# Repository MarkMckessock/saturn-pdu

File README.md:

# saturn-pdu

**A 1U rack PDU delivering six independently switched and metered 19V outputs,
for a six-node Minisforum MS-01 Kubernetes cluster.**

> **Status: draft specification. Nothing here has been built or bench-verified.**
> Every figure is analytical. Do not fabricate from this repository yet.

Derived from [Shrike-Lab/HomeLab-PDU-V1](https://github.com/Shrike-Lab/HomeLab-PDU-V1).
Licensed **CERN-OHL-S v2** (strongly reciprocal) -- see [`LICENSE`](LICENSE) and
[`NOTICE`](NOTICE).

---

## The problem

Six MS-01 nodes, six 180W bricks, six mains outlets, twelve cables, and no way
to see what any node draws or to power-cycle a wedged one without walking to the
rack.

## What this is

One 1U box: a single mains inlet, six 19V outputs, each switchable over the
network and each reporting volts, amps and watts.

```
IEC inlet ──► RSP-1000-48 ──► 48V bus ─┬──► [2ch board A] ──► ports 1,2
                  ▲                     ├──► [2ch board B] ──► ports 3,4
           remote ON/OFF                └──► [2ch board C] ──► ports 5,6
           (front button)                          │
                                          [control board]
                                          ESP32-S3 + wired Ethernet
                                          6x INA226 telemetry
                                          Prometheus /metrics
```

Each channel is an LM5116 synchronous buck, 48V down to 19V at 7A, with its own
fuse, its own current limit, and its own overvoltage crowbar that works **with
the microcontroller unpowered**.

## Three design rules that explain most of the decisions

1. **Outputs fail ON.** Channels are held on by resistors. The MCU can only turn
   one *off*, by actively pulling a pin down. An MCU that is crashed,
   unprogrammed, unpowered or physically removed leaves every node running.
   No firmware path may ever de-energise an output autonomously.
2. **Protection does not depend on software.** A shorted high-side transistor
   puts 48V on a 19V input and destroys a node. Disabling its controller
   achieves nothing when the transistor is a short, so each output carries an
   SCR crowbar with its own reference, powered from its own output.
3. **The display cannot break anything.** It is a separate device on a UART
   link, not the controller. Unplug it and all six outputs keep running and stay
   controllable over the network. A single tap can never de-energise a node.

## Honest cost comparison

About **$750-830** in parts, realistically **$900-1,100** for a first unit once
you budget the three board spins a first high-current layout needs. Six stock
bricks are $240-360.

A used switched-and-metered rack PDU (APC AP7921 class, $150-300) plugged into
your existing bricks gives you remote switching and per-outlet metering this
afternoon. **What this project buys over that is the 1U consolidation and the
elimination of six bricks -- a space and elegance goal, not a functional one.**
That is a fine reason to build it. It should just be the actual reason.

## Safety

**Read [`docs/safety.md`](docs/safety.md) before building or operating.**

The short version: the 19V outputs cannot shock you (IEC 62368-1 ES1), but a
live barrel plug dropped on a rack rail will melt itself. Unused ports stay off;
switch a port off before unplugging it. The mains side inside the chassis *can*
kill you -- unplug at the wall before opening the lid, and wait a minute.

## Repository layout

| Path | Contents |
|---|---|
| `params.yaml` | **Single source of truth.** Every dimension, rating and threshold used in more than one place. Docs, firmware and CAD all read from it |
| `docs/` | Specification, power budget, thermal, protection/FMEA, safety, upstream analysis, deviation log |
| `hardware/kicad/` | KiCad projects: 2-channel power board, control board, backplane |
| `cad/` | Parametric FreeCAD Python, plus STEP/STL exports |
| `firmware/` | ESPHome configuration for the control board and the display |
| `fab/` | Gerbers, BOM, pick-and-place |
| `reference/upstream-19in/` | Upstream's 19" B-rep solids, kept as dimensional reference |

## Build order

Stage-gated. **Do not order the full board set before stage 4 passes.**

| # | Stage | Gate |
|---|---|---|
| 0 | Measure the barrel jack and the real six-node draw | Both recorded |
| 1-2 | Schematics, BOM and sourcing | No unsourceable parts |
| 3 | LM5116 evaluation board, built and measured | A known-good reference exists |
| 4 | One 2-channel board: bring-up, fault injection, 72h burn-in, fault injection **again** | **Hard gate** |
| 5-6 | Control board, firmware, display, chassis | Fail-ON verified by pulling the MCU |
| 7 | **30-day canary on one worker node** | **Hard gate.** Any event resets to day zero |
| 8 | Remaining five nodes; control-plane nodes last | 24h six-node soak |

Full detail in [`docs/SPECIFICATION.md`](docs/SPECIFICATION.md) sections 8 and 9.

## Open items

Two measurements and one accepted risk. Both measurements carry provisional
values in `params.yaml` and neither blocks design work.

| ID | Item | Why it does not block |
|---|---|---|
| OPEN-5 | Barrel jack dimensions | Both candidate sizes share the same 8mm panel thread, so the panel cutout is identical. Only the part number is provisional |
| OPEN-6 | Real six-node peak draw | **Downgraded to informational.** The fitted RSP-1000-48 absorbs a reading 38% above estimate, so this validates the power budget rather than gating a purchase |
| R-0 | No independent design review | **Accepted, not resolved.** Bench testing and the 30-day canary stand in for it. Residual risk is moderate and knowingly taken |

## Contributing

This is a personal homelab project, not a product. Issues and observations are
welcome -- particularly from anyone with power-electronics experience, given
R-0. Pull requests are not expected.

Derivatives must remain under CERN-OHL-S v2 and must publish editable source,
not only exports. Upstream's source is in its git history; this repository keeps it in the tree.

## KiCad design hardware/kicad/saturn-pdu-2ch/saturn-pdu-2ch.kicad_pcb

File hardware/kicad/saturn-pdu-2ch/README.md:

# saturn-pdu-2ch — 2-channel power board

Open `saturn-pdu-2ch.kicad_pro` in KiCad 10.

| File | What it is | Made by |
|---|---|---|
| `saturn-pdu-2ch.kicad_sch`, `channel.kicad_sch` | Schematic. Top sheet + one channel sheet used twice (CH1, CH2) | `tools/gen_2ch_sch.py` (WP-4b) |
| `saturn-pdu-2ch.kicad_pcb` | Board: outline, holes, stackup, rules, every part loaded and linked | `tools/setup_2ch_pcb.py` (WP-4c) |
| `saturn-pdu-2ch.kicad_dru` | Custom design rules (48 V spacing, switch-node keep-away) | `tools/setup_2ch_pcb.py` |

**Both generator scripts are one-shot.** They overwrite their output. After any hand
edit, change the board from the schematic with *Tools → Update PCB from Schematic*
(F8), never by re-running a script.

## State at the end of WP-4c

- ERC: 0 errors, 0 warnings.
- DRC with schematic parity: **0 parity issues, no errors other than unrouted
  connections.** The remaining warnings are silkscreen labels overlapping each other,
  which go away as parts are spread out.
- Board: 90 × 130 mm, 2 mm corner radius (upstream's outline), 4 × M3 holes 4 mm in from
  each corner.
- Stackup: 4 layers, 2 oz outer / 1 oz inner, 1.62 mm, ENIG. The dielectric split is
  nominal — swap in the fab's own 2 oz stackup when ordering.
- In1.Cu has a full GND plane (press **B** to fill it). In2.Cu is free.

### Net classes

| Class | Nets | Track | Clearance |
|---|---|---|---|
| HV | +48V, VIN_F, SW, HB, HO, HO_G, SNUB | 1.0 mm | 0.2 mm (0.5 mm to non-HV copper, except pad-to-pad inside a part) |
| POWER | VOUT_REG, VOUT1/2, ISNS, GND | 2.0 mm | 0.2 mm |
| GATE | LO, LO_G | 0.5 mm | 0.2 mm |
| Default | everything else | 0.2 mm | 0.2 mm |

The track widths are only defaults. **Carry the 7 A paths in copper pours, not tracks.**

## Placement is a starting point, not a layout

Parts are packed in two columns, one per channel. Power flows from top (J1, 48 V in) to
bottom (J2, 19 V out). Each channel is a KiCad group, so it moves as one.

The order inside a column is roughly right, but the spacing is not. Do the layout
(WP-4d) with **TI's LM5116 EVM layout open beside it** (R-0 control 1). Put every place
you depart from it in `docs/deviations.md`.

## Layout checklist, most important first

1. **Hot loop as small as possible.** Input ceramics (C103–C106) → high-side FET (Q101) →
   low-side FET (Q102) → sense resistor (R103) → back to the ceramics' ground. Keep them
   side by side on the top layer, with the In1 GND plane directly underneath. This loop's
   size sets the switch-node spike, and the D-10 bench gate requires that spike to stay
   at or below 54 V.
2. **Keep the switch node (SW) small.** It only needs to join the FETs and L101. Don't
   pour extra copper on it. Keep it away from FB, CS, OVP_REF and I²C (a DRC rule
   enforces 1 mm).
3. **Kelvin sense.** CS and CSG are 0 Ω links (R104, R105). Route them as a close pair
   straight to R103's pads, not onto the power copper. Do the same for the INA226 inputs
   (VOUT_REG and VOUT) at R118's pads.
4. **Gate drive.** Run HO next to SW and LO next to GND, both short, from U101 to the
   FETs.
5. **Analog ground.** The LM5116 exposed pad is the star point. Place the FB divider
   (R112/R113), the compensation parts (R114, C118, C119) and the RT, SS, RAMP and VCC
   parts next to U101, grounded to its pad area rather than to the power path.
6. **Heat.** Put a thermal-via array under both FETs, into the In1 plane. The inductor,
   R103, R118 and R119 all need copper to spread heat into.
7. **Crowbar.** The SCR (Q105) goes near J2, across VOUT with short, wide copper. The
   OVP divider (R120/R121) senses at the output, not at the inductor.
8. **Snubber (R106/C108, not fitted).** Place it hard across Q102's drain and source so
   it works if it is ever needed.
9. **Connectors.** Pour +48V from J1 to both fuses. Run each VOUT to J2 pins as a pour
   and use both pins.

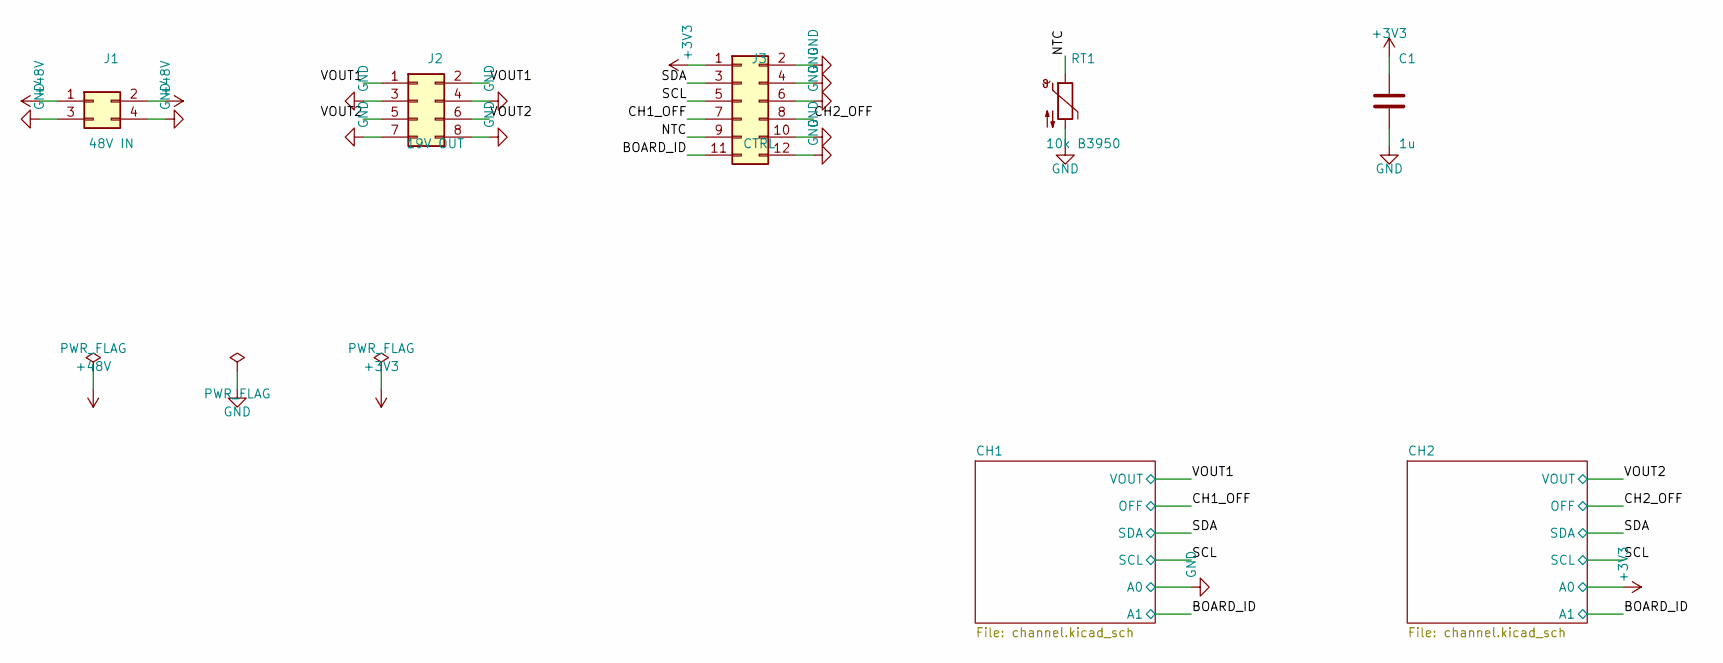
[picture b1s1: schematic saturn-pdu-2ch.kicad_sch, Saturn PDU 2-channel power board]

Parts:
C1: 1u; C_0603_1608Metric
J1: 48V IN; Molex_Mini-Fit_Jr_5566-04A_2x02_P4.20mm_Vertical; MPN Molex Mini-Fit Jr 5566-04A
J2: 19V OUT; Molex_Mini-Fit_Jr_5566-08A_2x04_P4.20mm_Vertical; MPN Molex Mini-Fit Jr 5566-08A
J3: CTRL; IDC-Header_2x06_P2.54mm_Vertical
RT1: 10k B3950; R_0603_1608Metric; MPN Murata NCP18XH103F03RB

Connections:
+3V3: C1.1, J3.1; also elsewhere on the board
+48V: J1.1, J1.2; also elsewhere on the board
/BOARD_ID: J3.11; also elsewhere on the board
/CH1_OFF: J3.7; also elsewhere on the board
/CH2_OFF: J3.8; also elsewhere on the board
/NTC: J3.9, RT1.1
/SCL: J3.5; also elsewhere on the board
/SDA: J3.3; also elsewhere on the board
/VOUT1: J2.1, J2.2; also elsewhere on the board
/VOUT2: J2.5, J2.6; also elsewhere on the board
GND: C1.2, J1.3, J1.4, J2.3, J2.4, J2.7, J2.8, J3.2, J3.4, J3.6, J3.10, J3.12, RT1.2; also elsewhere on the board

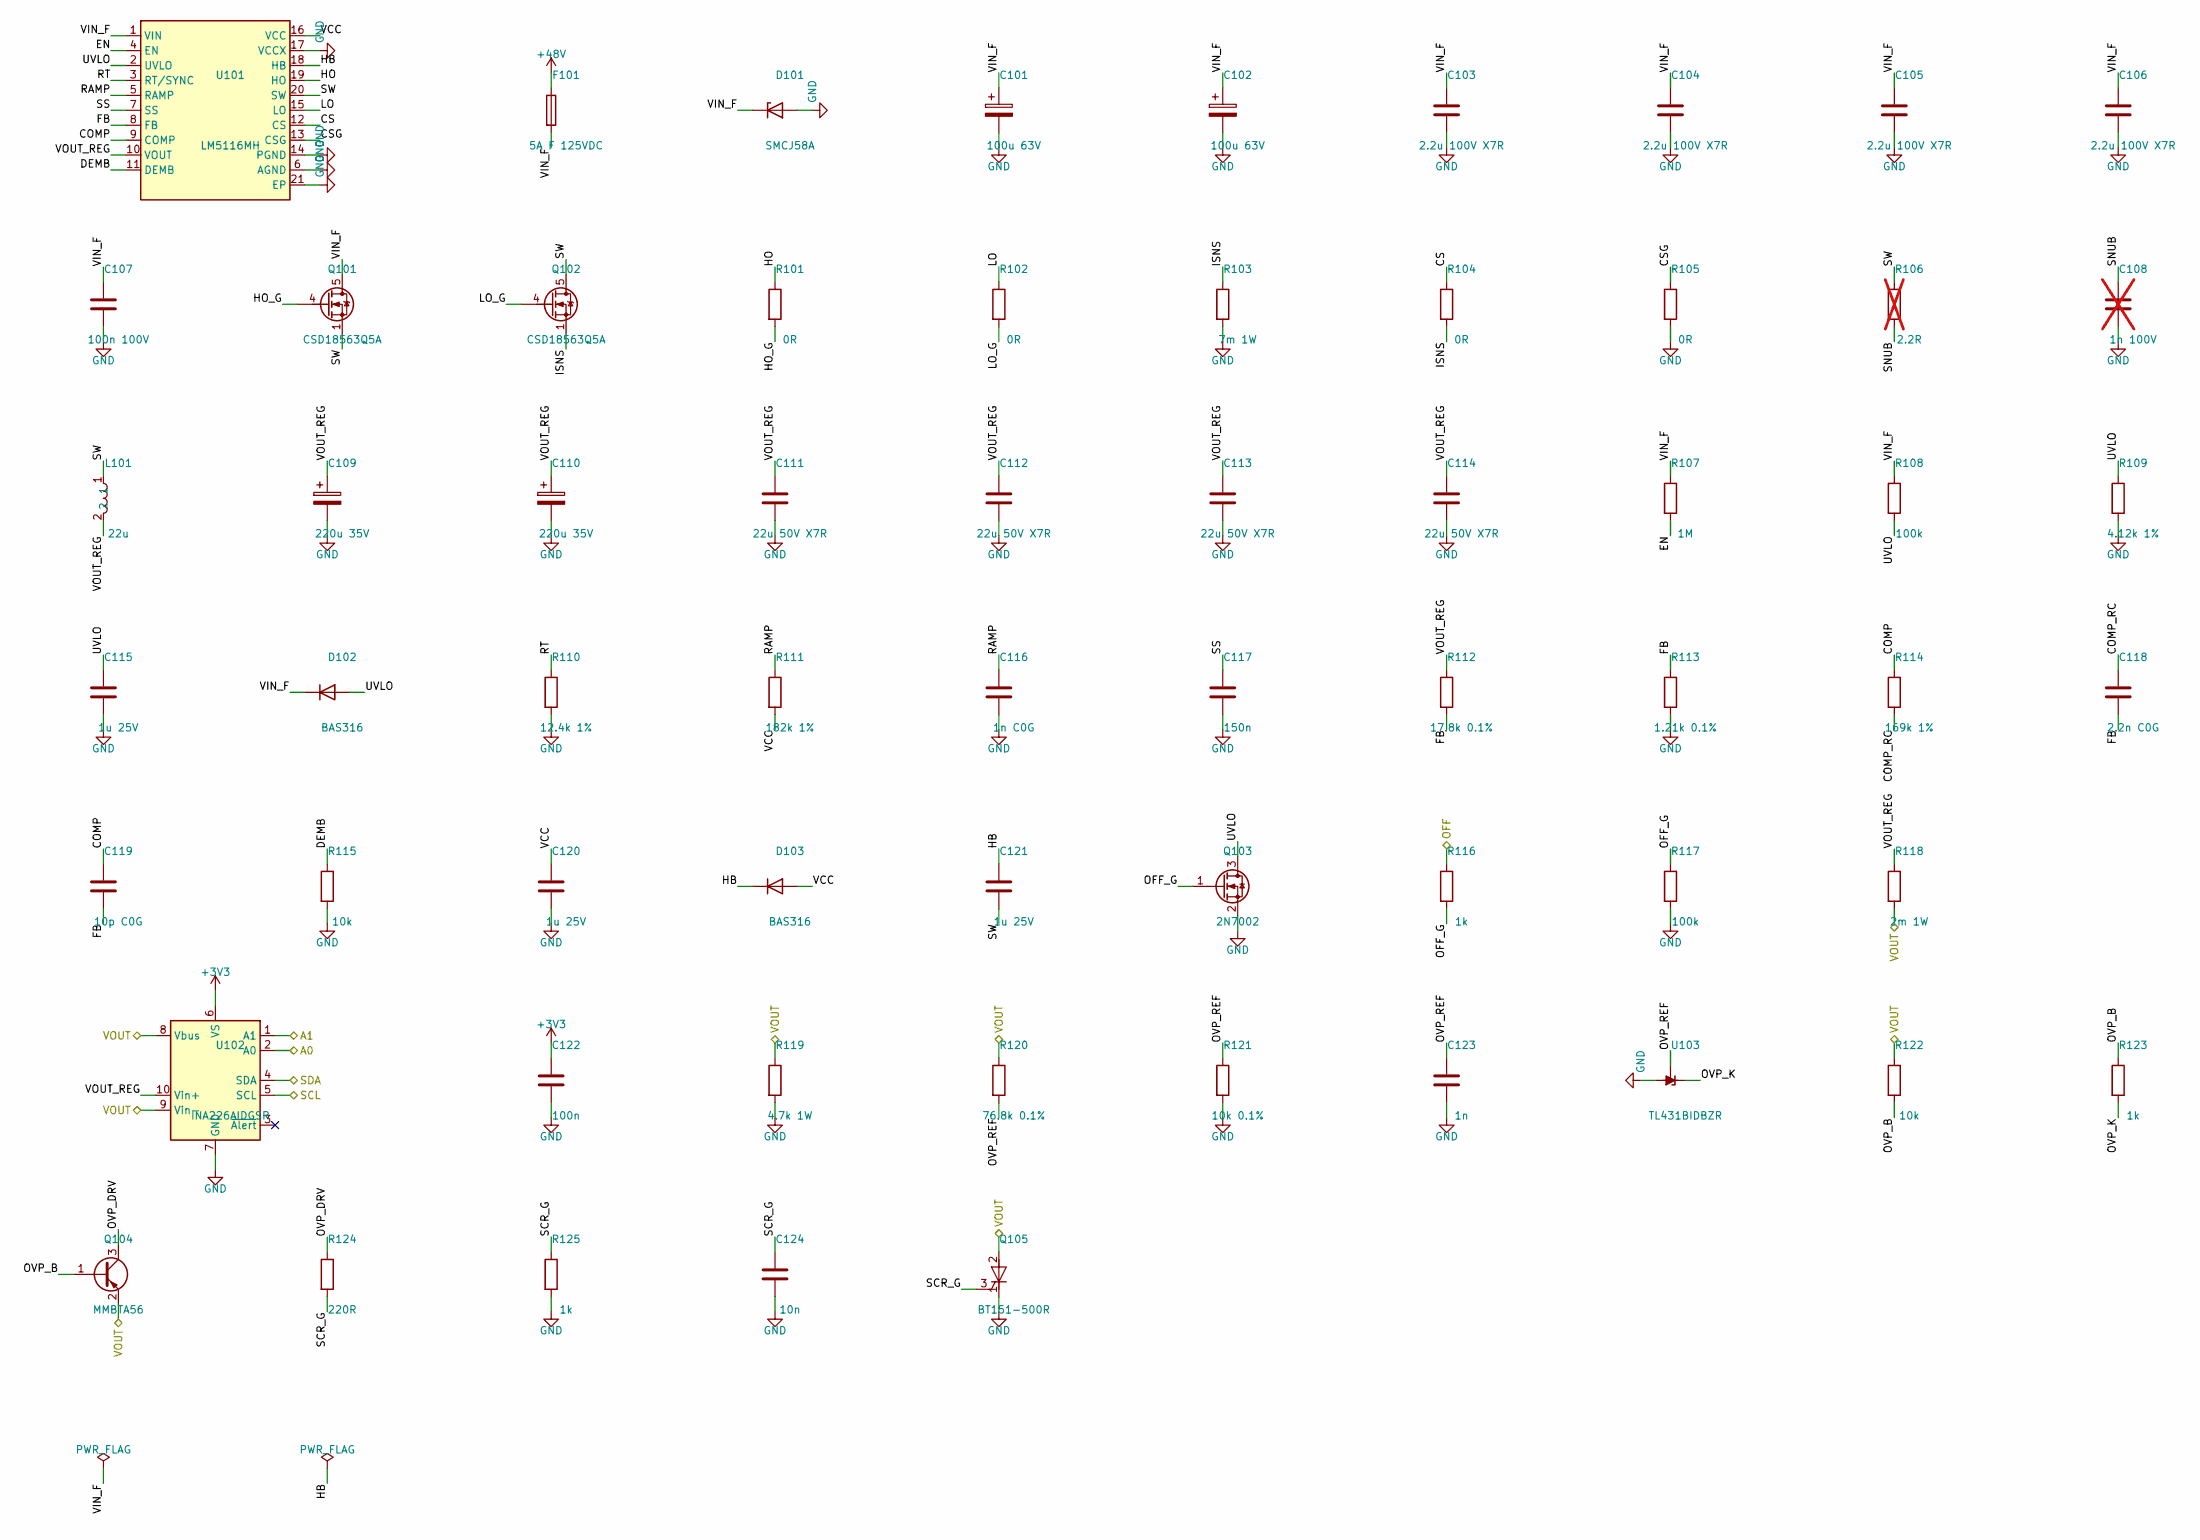
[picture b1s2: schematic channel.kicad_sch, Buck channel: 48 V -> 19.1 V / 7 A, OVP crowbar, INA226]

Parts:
C101, C102: 100u 63V; CP_Elec_10x10.5; MPN Panasonic EEEFK1J101P
C103, C104, C105, C106: 2.2u 100V X7R; C_1210_3225Metric; MPN Murata GRM32ER72A225KA35L
C107: 100n 100V; C_0805_2012Metric
C108: 1n 100V; C_0805_2012Metric; not fitted
C109, C110: 220u 35V; CP_Elec_8x10; MPN Panasonic EEHZA1V221P
C111, C112, C113, C114: 22u 50V X7R; C_1210_3225Metric; MPN Murata GRM32ER71H226KE15L
C115, C120, C121: 1u 25V; C_0603_1608Metric
C116: 1n C0G; C_0603_1608Metric
C117: 150n; C_0603_1608Metric
C118: 2.2n C0G; C_0603_1608Metric
C119: 10p C0G; C_0603_1608Metric
C122: 100n; C_0603_1608Metric
C123: 1n; C_0603_1608Metric
C124: 10n; C_0603_1608Metric
D101: SMCJ58A; D_SMC; MPN Littelfuse SMCJ58A
D102, D103: BAS316; D_SOD-323
F101: 5A F 125VDC; Fuse_Littelfuse-NANO2-451_453; MPN Littelfuse 0453005.MR
L101: 22u; L_Coilcraft_XAL1510; MPN Coilcraft XAL1510-223MEB
Q101, Q102: CSD18563Q5A; TI_VSONP-8_5x6mm_P1.27mm; MPN CSD18563Q5A
Q103: 2N7002; SOT-23
Q104: MMBTA56; SOT-23
Q105: BT151-500R; TO-220-3_Horizontal_TabDown; MPN WeEn BT151-500R
R101, R102, R104, R105: 0R; R_0603_1608Metric
R103: 7m 1W; R_2512_6332Metric; MPN Bourns CRA2512-FZ-R007ELF
R106: 2.2R; R_1206_3216Metric; not fitted
R107: 1M; R_0603_1608Metric
R108, R117: 100k; R_0603_1608Metric
R109: 4.12k 1%; R_0603_1608Metric
R110: 12.4k 1%; R_0603_1608Metric
R111: 182k 1%; R_0603_1608Metric
R112: 17.8k 0.1%; R_0603_1608Metric
R113: 1.21k 0.1%; R_0603_1608Metric
R114: 169k 1%; R_0603_1608Metric
R115, R122: 10k; R_0603_1608Metric
R116, R123, R125: 1k; R_0603_1608Metric
R118: 2m 1W; R_2512_6332Metric; MPN Vishay WSL2512R0020FEA
R119: 4.7k 1W; R_2512_6332Metric
R120: 76.8k 0.1%; R_0603_1608Metric
R121: 10k 0.1%; R_0603_1608Metric
R124: 220R; R_0805_2012Metric
U101: LM5116MH; ETSSOP-20-1EP_4.4x6.5mm_P0.65mm_EP3x4.2mm; MPN LM5116MHX/NOPB
U102: INA226AIDGSR; TSSOP-10_3x3mm_P0.5mm
U103: TL431BIDBZR; SOT-23

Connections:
+3V3: C122.1, U102.6 (VS); also elsewhere on the board
+48V: F101.1; also elsewhere on the board
/BOARD_ID: U102.1 (A1); also elsewhere on the board
/CH1/COMP: C119.1, R114.1, U101.9 (COMP)
/CH1/COMP_RC: C118.1, R114.2
/CH1/CS: R104.1, U101.12 (CS)
/CH1/CSG: R105.1, U101.13 (CSG)
/CH1/DEMB: R115.1, U101.11 (DEMB)
/CH1/EN: R107.2, U101.4 (EN)
/CH1/FB: C118.2, C119.2, R112.2, R113.1, U101.8 (FB)
/CH1/HB: C121.1, D103.1 (K), U101.18 (HB)
/CH1/HO: R101.1, U101.19 (HO)
/CH1/HO_G: Q101.4 (G), R101.2
/CH1/ISNS: Q102.1 (S), Q102.2 (S), Q102.3 (S), R103.1, R104.2
/CH1/LO: R102.1, U101.15 (LO)
/CH1/LO_G: Q102.4 (G), R102.2
/CH1/OFF_G: Q103.1 (G), R116.2, R117.1
/CH1/OVP_B: Q104.1 (B), R122.2, R123.1
/CH1/OVP_DRV: Q104.3 (C), R124.1
/CH1/OVP_K: R123.2, U103.1 (K)
/CH1/OVP_REF: C123.1, R120.2, R121.1, U103.2 (REF)
/CH1/RAMP: C116.1, R111.1, U101.5 (RAMP)
/CH1/RT: R110.1, U101.3 (RT/SYNC)
/CH1/SCR_G: C124.1, Q105.3 (G), R124.2, R125.1
/CH1/SNUB: C108.1, R106.2
/CH1/SS: C117.1, U101.7 (SS)
/CH1/SW: C121.2, L101.1, Q101.1 (S), Q101.2 (S), Q101.3 (S), Q102.5 (D), R106.1, U101.20 (SW)
/CH1/UVLO: C115.1, D102.2 (A), Q103.3 (D), R108.2, R109.1, U101.2 (UVLO)
/CH1/VCC: C120.1, D103.2 (A), R111.2, U101.16 (VCC)
/CH1/VIN_F: C101.1, C102.1, C103.1, C104.1, C105.1, C106.1, C107.1, D101.1 (K), D102.1 (K), F101.2, Q101.5 (D), R107.1, R108.1, U101.1 (VIN)
/CH1/VOUT_REG: C109.1, C110.1, C111.1, C112.1, C113.1, C114.1, L101.2, R112.1, R118.1, U101.10 (VOUT), U102.10 (Vin+)
/CH1_OFF: R116.1; also elsewhere on the board
/SCL: U102.5 (SCL); also elsewhere on the board
/SDA: U102.4 (SDA); also elsewhere on the board
/VOUT1: Q104.2 (E), Q105.2 (A), R118.2, R119.1, R120.1, R122.1, U102.8 (Vbus), U102.9 (Vin-); also elsewhere on the board
GND: C101.2, C102.2, C103.2, C104.2, C105.2, C106.2, C107.2, C108.2, C109.2, C110.2, C111.2, C112.2, C113.2, C114.2, C115.2, C116.2, C117.2, C120.2, C122.2, C123.2, C124.2, D101.2 (A), Q103.2 (S), Q105.1 (K), R103.2, R105.2, R109.2, R110.2, R113.2, R115.2, R117.2, R119.2, R121.2, R125.2, U101.6 (AGND), U101.14 (PGND), U101.17 (VCCX), U101.21 (EP), U102.2 (A0), U102.7 (GND), U103.3 (A); also elsewhere on the board

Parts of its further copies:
C201, C202: 100u 63V; CP_Elec_10x10.5; MPN Panasonic EEEFK1J101P
C203, C204, C205, C206: 2.2u 100V X7R; C_1210_3225Metric; MPN Murata GRM32ER72A225KA35L
C207: 100n 100V; C_0805_2012Metric
C208: 1n 100V; C_0805_2012Metric; not fitted
C209, C210: 220u 35V; CP_Elec_8x10; MPN Panasonic EEHZA1V221P
C211, C212, C213, C214: 22u 50V X7R; C_1210_3225Metric; MPN Murata GRM32ER71H226KE15L
C215, C220, C221: 1u 25V; C_0603_1608Metric
C216: 1n C0G; C_0603_1608Metric
C217: 150n; C_0603_1608Metric
C218: 2.2n C0G; C_0603_1608Metric
C219: 10p C0G; C_0603_1608Metric
C222: 100n; C_0603_1608Metric
C223: 1n; C_0603_1608Metric
C224: 10n; C_0603_1608Metric
D201: SMCJ58A; D_SMC; MPN Littelfuse SMCJ58A
D202, D203: BAS316; D_SOD-323
F201: 5A F 125VDC; Fuse_Littelfuse-NANO2-451_453; MPN Littelfuse 0453005.MR
L201: 22u; L_Coilcraft_XAL1510; MPN Coilcraft XAL1510-223MEB
Q201, Q202: CSD18563Q5A; TI_VSONP-8_5x6mm_P1.27mm; MPN CSD18563Q5A
Q203: 2N7002; SOT-23
Q204: MMBTA56; SOT-23
Q205: BT151-500R; TO-220-3_Horizontal_TabDown; MPN WeEn BT151-500R
R201, R202, R204, R205: 0R; R_0603_1608Metric
R203: 7m 1W; R_2512_6332Metric; MPN Bourns CRA2512-FZ-R007ELF
R206: 2.2R; R_1206_3216Metric; not fitted
R207: 1M; R_0603_1608Metric
R208, R217: 100k; R_0603_1608Metric
R209: 4.12k 1%; R_0603_1608Metric
R210: 12.4k 1%; R_0603_1608Metric
R211: 182k 1%; R_0603_1608Metric
R212: 17.8k 0.1%; R_0603_1608Metric
R213: 1.21k 0.1%; R_0603_1608Metric
R214: 169k 1%; R_0603_1608Metric
R215, R222: 10k; R_0603_1608Metric
R216, R223, R225: 1k; R_0603_1608Metric
R218: 2m 1W; R_2512_6332Metric; MPN Vishay WSL2512R0020FEA
R219: 4.7k 1W; R_2512_6332Metric
R220: 76.8k 0.1%; R_0603_1608Metric
R221: 10k 0.1%; R_0603_1608Metric
R224: 220R; R_0805_2012Metric
U201: LM5116MH; ETSSOP-20-1EP_4.4x6.5mm_P0.65mm_EP3x4.2mm; MPN LM5116MHX/NOPB
U202: INA226AIDGSR; TSSOP-10_3x3mm_P0.5mm
U203: TL431BIDBZR; SOT-23

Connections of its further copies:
+3V3: C222.1, U202.2 (A0), U202.6 (VS); also elsewhere on the board
+48V: F201.1; also elsewhere on the board
/BOARD_ID: U202.1 (A1); also elsewhere on the board
/CH2/COMP: C219.1, R214.1, U201.9 (COMP)
/CH2/COMP_RC: C218.1, R214.2
/CH2/CS: R204.1, U201.12 (CS)
/CH2/CSG: R205.1, U201.13 (CSG)
/CH2/DEMB: R215.1, U201.11 (DEMB)
/CH2/EN: R207.2, U201.4 (EN)
/CH2/FB: C218.2, C219.2, R212.2, R213.1, U201.8 (FB)
/CH2/HB: C221.1, D203.1 (K), U201.18 (HB)
/CH2/HO: R201.1, U201.19 (HO)
/CH2/HO_G: Q201.4 (G), R201.2
/CH2/ISNS: Q202.1 (S), Q202.2 (S), Q202.3 (S), R203.1, R204.2
/CH2/LO: R202.1, U201.15 (LO)
/CH2/LO_G: Q202.4 (G), R202.2
/CH2/OFF_G: Q203.1 (G), R216.2, R217.1
/CH2/OVP_B: Q204.1 (B), R222.2, R223.1
/CH2/OVP_DRV: Q204.3 (C), R224.1
/CH2/OVP_K: R223.2, U203.1 (K)
/CH2/OVP_REF: C223.1, R220.2, R221.1, U203.2 (REF)
/CH2/RAMP: C216.1, R211.1, U201.5 (RAMP)
/CH2/RT: R210.1, U201.3 (RT/SYNC)
/CH2/SCR_G: C224.1, Q205.3 (G), R224.2, R225.1
/CH2/SNUB: C208.1, R206.2
/CH2/SS: C217.1, U201.7 (SS)
/CH2/SW: C221.2, L201.1, Q201.1 (S), Q201.2 (S), Q201.3 (S), Q202.5 (D), R206.1, U201.20 (SW)
/CH2/UVLO: C215.1, D202.2 (A), Q203.3 (D), R208.2, R209.1, U201.2 (UVLO)
/CH2/VCC: C220.1, D203.2 (A), R211.2, U201.16 (VCC)
/CH2/VIN_F: C201.1, C202.1, C203.1, C204.1, C205.1, C206.1, C207.1, D201.1 (K), D202.1 (K), F201.2, Q201.5 (D), R207.1, R208.1, U201.1 (VIN)
/CH2/VOUT_REG: C209.1, C210.1, C211.1, C212.1, C213.1, C214.1, L201.2, R212.1, R218.1, U201.10 (VOUT), U202.10 (Vin+)
/CH2_OFF: R216.1; also elsewhere on the board
/SCL: U202.5 (SCL); also elsewhere on the board
/SDA: U202.4 (SDA); also elsewhere on the board
/VOUT2: Q204.2 (E), Q205.2 (A), R218.2, R219.1, R220.1, R222.1, U202.8 (Vbus), U202.9 (Vin-); also elsewhere on the board
GND: C201.2, C202.2, C203.2, C204.2, C205.2, C206.2, C207.2, C208.2, C209.2, C210.2, C211.2, C212.2, C213.2, C214.2, C215.2, C216.2, C217.2, C220.2, C222.2, C223.2, C224.2, D201.2 (A), Q203.2 (S), Q205.1 (K), R203.2, R205.2, R209.2, R210.2, R213.2, R215.2, R217.2, R219.2, R221.2, R225.2, U201.6 (AGND), U201.14 (PGND), U201.17 (VCCX), U201.21 (EP), U202.7 (GND), U203.3 (A); also elsewhere on the board

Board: 4 copper layers, 133 parts (0 on the bottom side), 67 nets, no tracks yet.

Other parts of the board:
H1, H2, H3, H4: MountingHole_3.2mm_M3

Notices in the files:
hardware/kicad/saturn-pdu-2ch/channel.kicad_sch:
saturn-pdu (CERN-OHL-S-2.0)
hardware/kicad/saturn-pdu-2ch/saturn-pdu-2ch.kicad_pcb:
CERN-OHL-S-2.0
parts and their libraries:
TI VSONP-8 5x6mm (Q5A NexFET package), pads renumbered to datasheet: 1-3 S, 4 G, 5 D (all drain). Derived from KiCad Package_SON:VSONP-8-1EP_5x6_P1.27mm (CC-BY-SA 4.0). Verified against TI CSD18563Q5A SLPS444C recommended land pattern.
